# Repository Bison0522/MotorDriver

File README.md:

# MotorDriver

必ずマザーに220μF以上のコンデンサを一つ以上取り付けること．このコンデンサをつけなかったことで燃えた場合，その原因はモータによる逆起電圧がFETの定格電圧を超えたことであり，たいていはFETとTLPをすべて取り換えることで直すことができる．ただし，モータの電源でなくロジックの12Vに何らかのノイズが乗ったと思われる場合（モータとロジックの電源が共通であったなど）はこの限りではなく，ブートストラップ用（FETと同じ面に2つ実装．裏面の大きい4つのダイオードではない）のダイオードなどが故障している可能性がある．余裕があれば新しいものを使用するべきである．

i2cアドレスは，DIPスイッチの#1が最下位ビットである．よって#1=on,#2=off,#3=off,#4=offであれば0b0001000=0x08である．
Nucleoの場合，7bitのi2cアドレスに加え，最下位にRWビット（モータードライバはWrite限定のため0）を追加し8bit=1byteとして設定する必要があるため，0x10がこの時のスレーブアドレスとなる．

GMDB2-Dは単体，E-ASSEMBLEが発注用に面付したもの．E.zipを発注すればよい．名前が違うのは，Eにする際にDに上書きしたので名前がそのままなだけで深い意味はない．

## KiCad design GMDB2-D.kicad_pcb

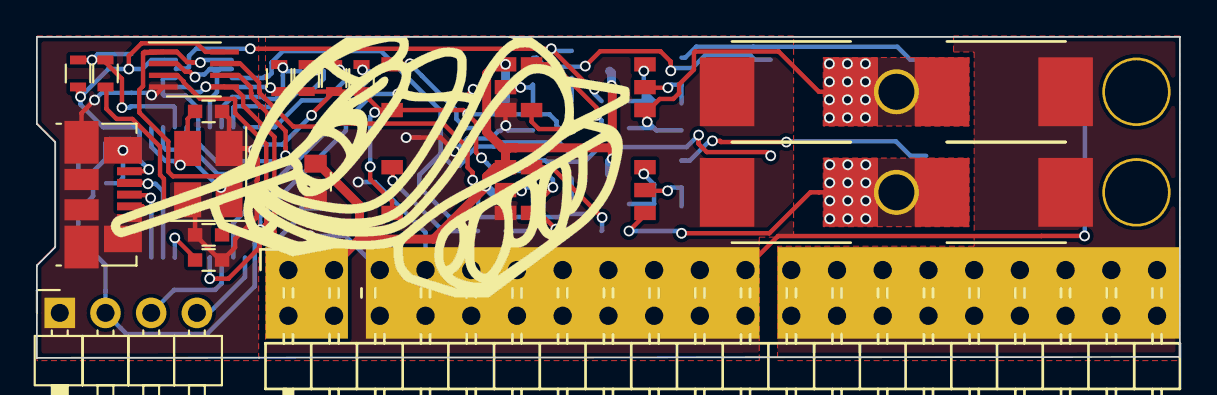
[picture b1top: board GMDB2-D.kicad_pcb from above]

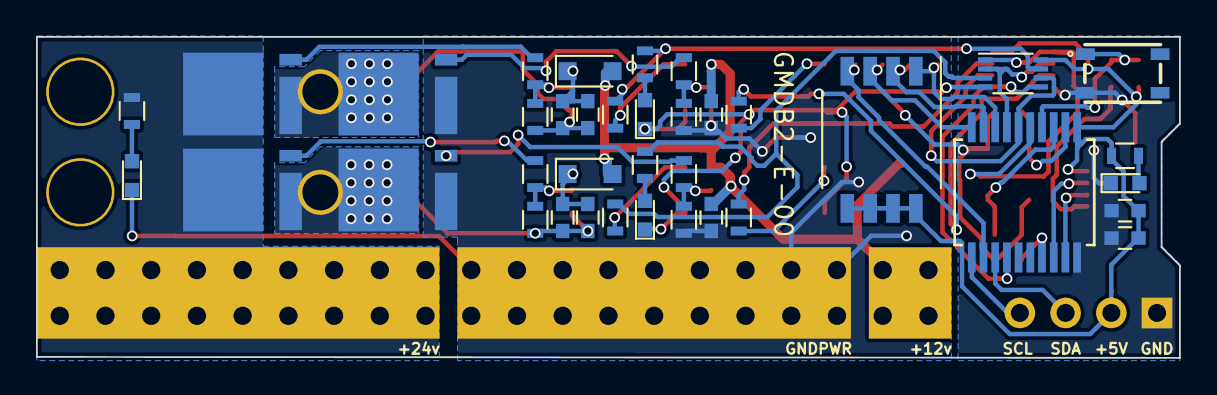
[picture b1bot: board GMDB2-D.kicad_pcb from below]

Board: 2 copper layers, 63.5 x 17.8 mm, 63 parts (38 on the bottom side), 46 nets.

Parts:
C1, C3, C4, C5, C6, C8, C9, C10: 0.1u; C_0603
C2: 1u; C_0603
C7: 22u; C_0805
C11, C12: C; C_0603
D1, D2, D3, D7: LED; LED_0603
D4, D10: SBD; D_SOD-323_HandSoldering
D5, D6, D8, D9: SBD; SKB-SK54
J1: USB_Micro; USB_Micro-B_Molex_47346-0001
J2: I2C; PIN4
J4: POWER; Pin_Header_Angled_2x20
Q1, Q2, Q3, Q4: NchFET; STL120N8F7
R1: JP; R_0603
R2, R3, R4, R5, R6, R12, R13, R19, R20: 10k; R_0603
R7, R8, R9, R10, R11, R21, R22: 510; R_0603
R14, R15, R17, R18: 47; R_0603
R16: 4.7k; R_0603
S1: SKRPACE010; tactsw
SW1: ADDRESS; dipsw
U1: PIC18F14K50-I/SS; PIC18F14K50
U2: AND2; VSSOP-8_2.3x2mm_Pitch0.5mm
U3, U4, U5, U6: TLP152
U7: OR2; SSOP-8_2.95x2.8mm_Pitch0.65mm
Y1: Crystal_GND24; Crystal_SMD_EuroQuartz_MT-4pin_3.2x2.5mm_HandSoldering
hoge: HOLE
via: v; via

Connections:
*MCLR: R1.1, R6.2, S1.1, U1.4
+5V: C1.1, C2.1, J1.1, J2.2, R6.1, R7.1, SW1.5, SW1.6, SW1.7, SW1.8, U1.1, U2.8, U7.8
+12V: C5.1, C7.1, C10.1, D4.2, D10.2, J4.1, U4.6, U6.6
+24V: D5.1, D8.1, J4.3, Q1.1, Q3.1, R16.1
CCW: U1.14, U2.5, U7.5
CW: U1.7, U2.2, U7.2
GND: C1.2, C2.2, C3.1, C11.1, C12.2, D1.1, D2.1, D3.1, J1.5, J1.6, J2.1, R2.2, R3.2, R4.2, R5.2, S1.3, U1.20, U2.4, U3.3, U4.3, U5.3, U6.3, U7.4, Y1.2, Y1.4
GNDPWR: C5.2, C7.2, C10.2, D6.2, D7.1, D9.2, J4.2, Q2.3, Q4.3, R13.2, R20.2, U4.4, U6.4
unnamed: C3.2, U1.17
unnamed: C4.1, C6.1, D4.1, U3.6
unnamed: C4.2, C6.2, D5.2, D6.1, Q1.3, Q2.1, R12.2, U3.4, hoge.1
unnamed: C8.1, C9.1, D10.1, U5.6
unnamed: C8.2, C9.2, D8.2, D9.1, Q3.3, Q4.1, R19.2, U5.4
unnamed: C11.2, U1.3, Y1.1
unnamed: C12.1, U1.2, Y1.3
unnamed: D1.2, R7.2
unnamed: D2.2, R10.2
unnamed: D3.2, R11.2
unnamed: D7.2, R16.2
unnamed: J1.4, R1.2
unnamed: Q1.2, R14.1
unnamed: Q2.2, R15.1
unnamed: Q3.2, R17.1
unnamed: Q4.2, R18.1
unnamed: R2.1, SW1.3, U1.10
unnamed: R3.1, SW1.2, U1.9
unnamed: R4.1, SW1.1, U1.8
unnamed: R5.1, SW1.4, U1.12
unnamed: R8.1, U3.1
unnamed: R9.1, U4.1
unnamed: R12.1, R14.2, U3.5
unnamed: R13.1, R15.2, U4.5
unnamed: R17.2, R19.1, U5.5
unnamed: R18.2, R20.1, U6.5
unnamed: R21.1, U5.1
unnamed: R22.1, U6.1
PGC/D-: J1.2, U1.18
PGD/D+: J1.3, U1.19
PWM-A: U1.5, U2.1, U7.1
PWM-A-AND: R8.2, R10.1, U2.7
PWM-A-OR: R22.2, U7.7
PWM-B: U1.6, U2.6, U7.6
PWM-B-AND: R11.1, R21.2, U2.3
PWM-B-OR: R9.2, U7.3
SCL: J2.4, U1.11
SDA: J2.3, U1.13

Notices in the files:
parts and their libraries:
Copyright 2016 Accelerated Designs. All rights reserved.
